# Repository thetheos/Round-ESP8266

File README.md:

# Round-ESP8266
carte micro-controller ESP8266 intégre à un pcb rond avec pile lithium et rechage via QI

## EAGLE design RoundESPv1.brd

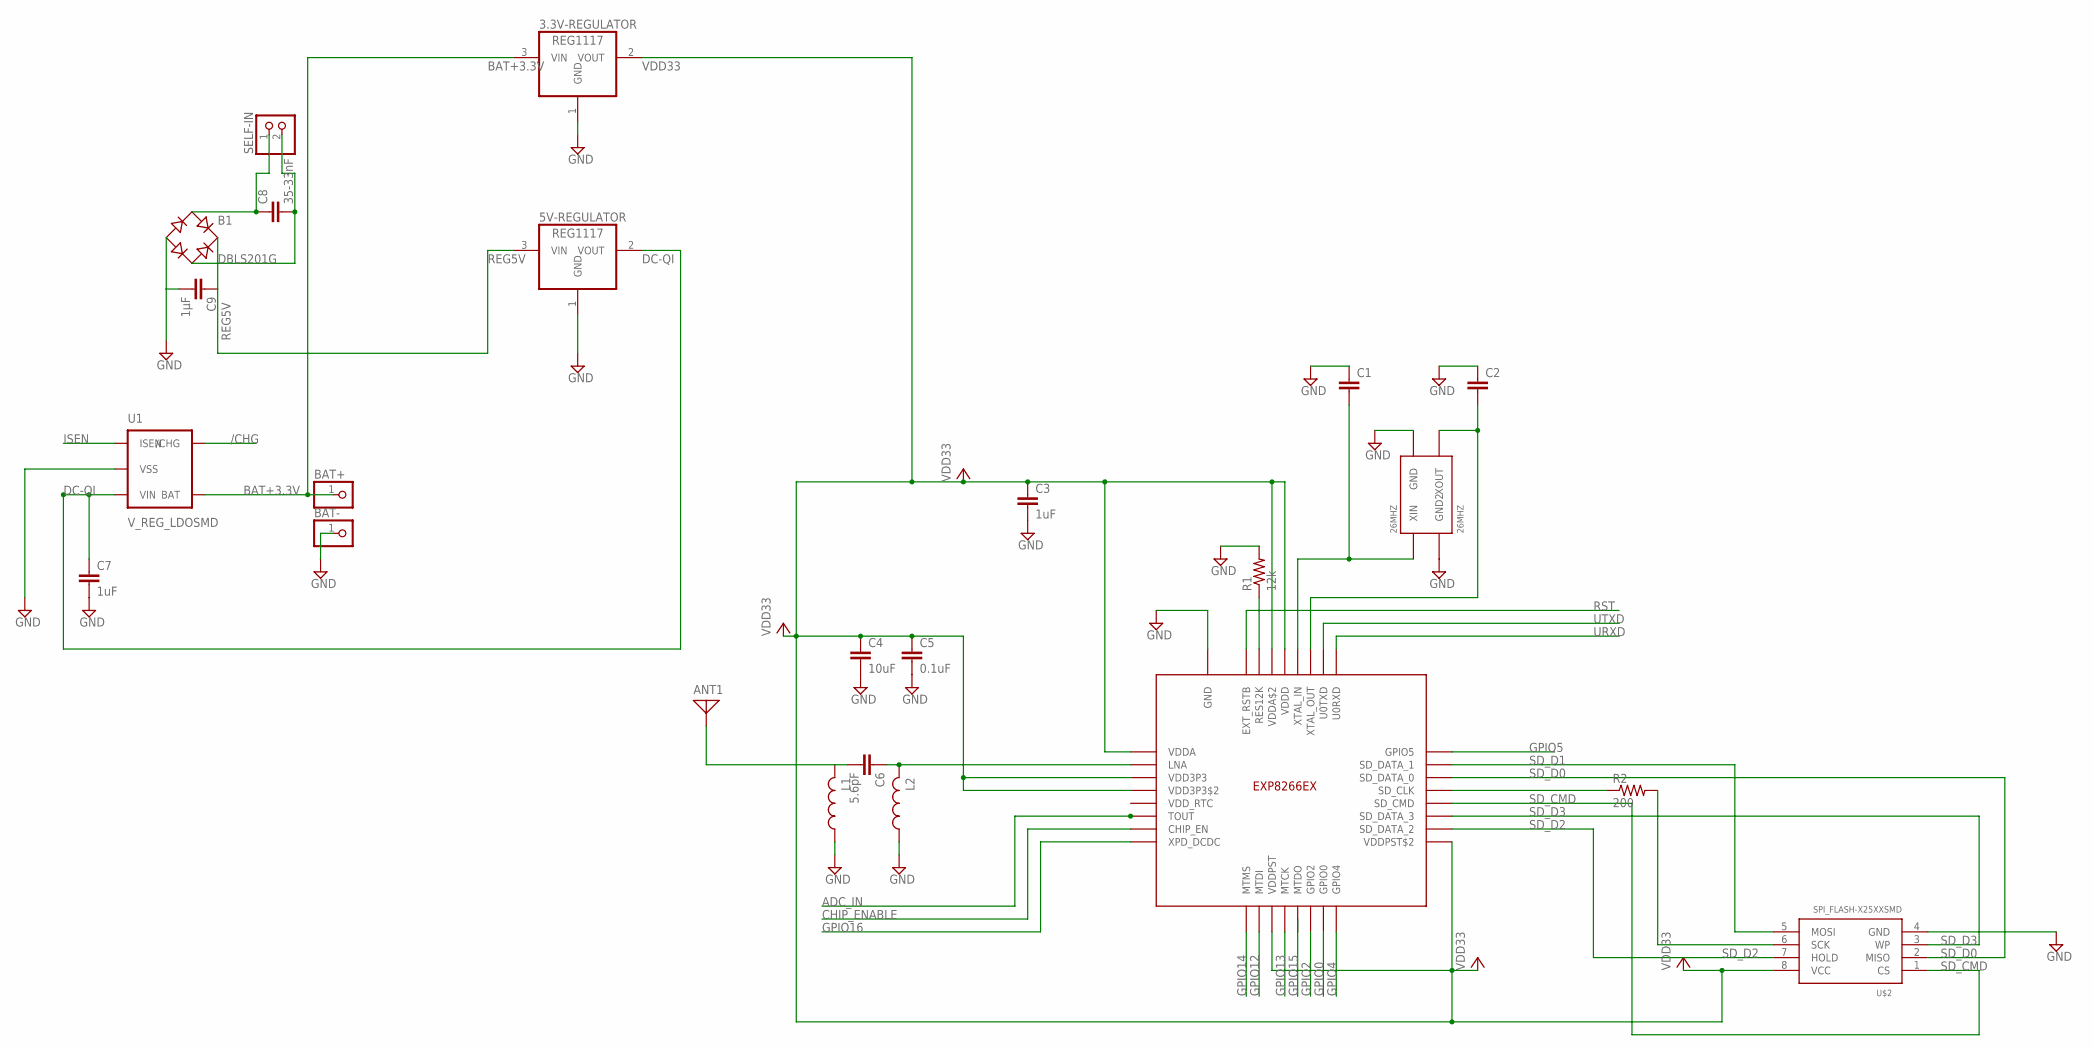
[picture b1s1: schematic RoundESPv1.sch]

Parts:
3.3V-REGULATOR, 5V-REGULATOR: REG1117; SOT223
26MHZ: 26MHZ; CRYSTAL-OSC-SMD-5X3.2
ANT1: ANTENNA; PAD-01
B1: DBLS201G; DBS
BAT+: PINHD-1X1; 1X01
BAT-: PINHD-1X1; 1X01
C1, C2: C2,5-3; C2.5-3
C3, C7: 1uF; C2.5-3
C4: 10uF; C2.5-3
C5: 0.1uF; C2.5-3
C6: 5.6pF; C2.5-3
C8: 35-33nF; C2.5-3
C9: 1µF; C2.5-3
L1, L2: L-USL2012C; L2012C
R1: 12k; M0805
R2: 200; M0805
SELF-IN: PINHD-1X2; 1X02
U1: V_REG_LDOSMD; SOT23-5
U2: ESP8266EX
U$2: SPI_FLASH-X25XXSMD; SO08

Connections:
/CHG: U1.5 (/CHG)
ADC_IN: U2.TOUT
BAT+3.3V: 3.3V-REGULATOR.3 (VIN), BAT+.1, U1.4 (BAT)
CHIP_ENABLE: U2.CHIP_EN
DC-QI: 5V-REGULATOR.2 (VOUT), C7.1, U1.2 (VIN)
GND: 3.3V-REGULATOR.1 (GND), 5V-REGULATOR.1 (GND), 26MHZ.1 (GND2), 26MHZ.3 (GND), B1.-, BAT-.1, C1.1, C2.1, C3.2, C4.2, C5.2, C7.2, C9.2, L1.1, L2.1, R1.2, U1.3 (VSS), U2.GND, U$2.4 (GND)
GPIO0: U2.GPIO0
GPIO2: U2.GPIO2
GPIO4: U2.GPIO4
GPIO5: U2.GPOIO5 (GPIO5)
GPIO12: U2.MTDI
GPIO13: U2.MTCK
GPIO14: U2.MTMS
GPIO15: U2.MTDO
GPIO16: U2.XPD_DCDC
ISEN: U1.1 (ISEN)
unnamed: 26MHZ.2 (XOUT), C2.2, U2.XTAL_OUT
unnamed: C6.1, L2.2, U2.LNA
unnamed: ANT1.1, C6.2, L1.2
unnamed: 26MHZ.4 (XIN), C1.2, U2.XTAL_IN
unnamed: R1.1, U2.RES12K
unnamed: B1.AC1, C8.1, SELF-IN.1
unnamed: B1.AC2, C8.2, SELF-IN.2
unnamed: R2.1, U2.SD_CLK
unnamed: R2.2, U$2.6 (SCK)
REG5V: 5V-REGULATOR.3 (VIN), B1.+, C9.1
RST: U2.EXT_RSTB
SD_CMD: U2.SD_CMD, U$2.1 (CS)
SD_D0: U2.SD_DATA_0, U$2.2 (MISO)
SD_D1: U2.SD_DATA_1, U$2.5 (MOSI)
SD_D2: U2.SD_DATA_2, U$2.7 (HOLD)
SD_D3: U2.SD_DATA_3, U$2.3 (WP)
URXD: U2.U0RXD
UTXD: U2.U0TXD
VDD33: 3.3V-REGULATOR.2 (VOUT), C3.1, C4.1, C5.1, U2.VDD3P3, U2.VDD3P3$2, U2.VDDA, U2.VDDA$2, U2.VDDD, U2.VDDPST, U2.VDDPST$2, U$2.8 (VCC)

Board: 4 copper layers, 24 parts (0 on the bottom side), 19 nets, no tracks yet.

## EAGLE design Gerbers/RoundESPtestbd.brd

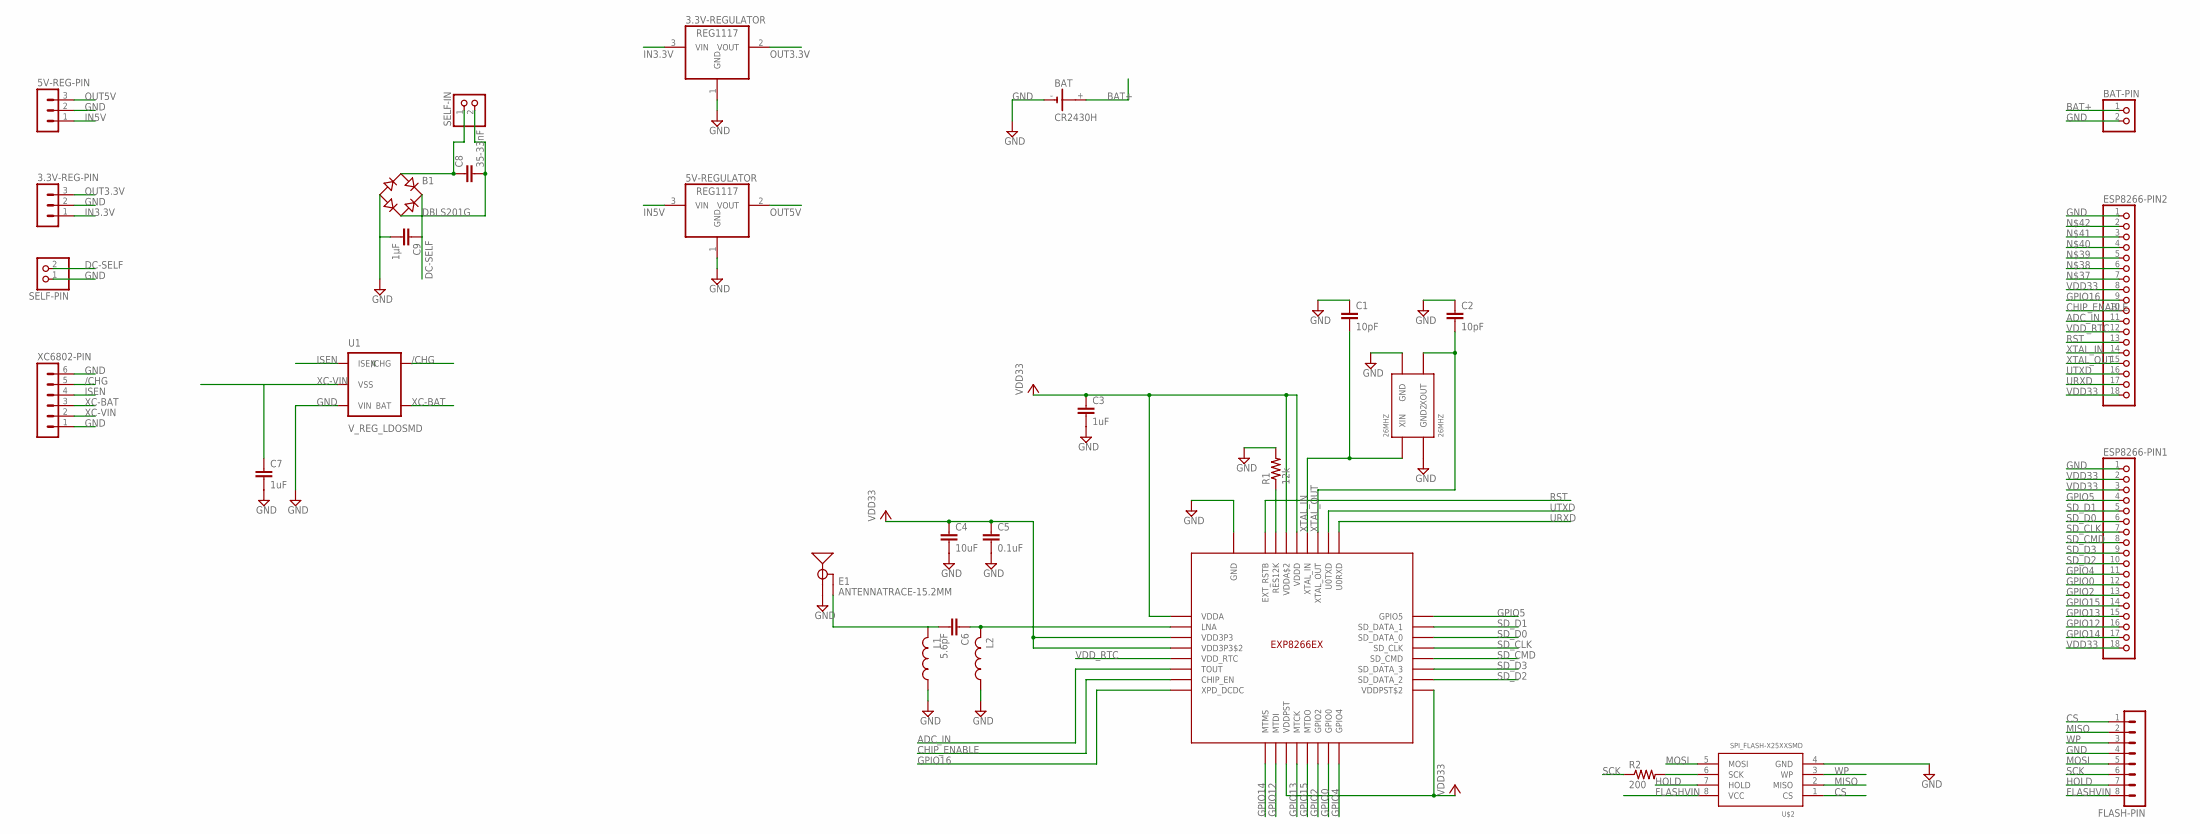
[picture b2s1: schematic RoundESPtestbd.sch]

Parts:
3.3V-REG-PIN, 5V-REG-PIN: MA03-1
3.3V-REGULATOR, 5V-REGULATOR: REG1117; SOT223
26MHZ: 26MHZ; CRYSTAL-OSC-SMD-5X3.2
B1: DBLS201G; DBS
BAT: CR2430H
BAT-PIN: PINHD-1X2; 1X02
C1, C2: 10pF; C2.5-3
C3, C7: 1uF; C2.5-3
C4: 10uF; C2.5-3
C5: 0.1uF; C2.5-3
C6: 5.6pF; C2.5-3
C8: 35-33nF; C2.5-3
C9: 1µF; C2.5-3
E1: ANTENNATRACE-15.2MM; TRACE_ANTENNA_2.4GHZ_15.2MM
ESP8266-PIN1, ESP8266-PIN2: PINHD-1X18; 1X18
FLASH-PIN: MA08-1
L1, L2: L-USL2012C; L2012C
R1: 12k; M0805
R2: 200; M0805
SELF-IN: PINHD-1X2; 1X02
SELF-PIN: PINHD-1X2; 1X02
U1: V_REG_LDOSMD; SOT23-5
U2: ESP8266EX
U$2: SPI_FLASH-X25XXSMD; SO08
XC6802-PIN: MA06-1

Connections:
111: R2.2, U$2.6 (SCK)
/CHG: U1.5 (/CHG), XC6802-PIN.5
ADC_IN: ESP8266-PIN2.11, U2.TOUT
BAT+: BAT.+, BAT-PIN.1
CHIP_ENABLE: ESP8266-PIN2.10, U2.CHIP_EN
CS: FLASH-PIN.1, U$2.1 (CS)
DC-SELF: B1.+, C9.1, SELF-PIN.2
FLASHVIN: FLASH-PIN.8, U$2.8 (VCC)
GND: 3.3V-REG-PIN.2, 3.3V-REGULATOR.1 (GND), 5V-REG-PIN.2, 5V-REGULATOR.1 (GND), 26MHZ.1 (GND2), 26MHZ.3 (GND), B1.-, BAT.-, BAT-PIN.2, C1.1, C2.1, C3.2, C4.2, C5.2, C9.2, E1.ANT (SIGNAL), ESP8266-PIN1.1, ESP8266-PIN2.1, FLASH-PIN.4, L1.1, L2.1, R1.2, SELF-PIN.1, U1.2 (VIN), U2.GND, U$2.4 (GND), XC6802-PIN.1, XC6802-PIN.6
GPIO0: ESP8266-PIN1.12, U2.GPIO0
GPIO2: ESP8266-PIN1.13, U2.GPIO2
GPIO4: ESP8266-PIN1.11, U2.GPIO4
GPIO5: ESP8266-PIN1.4, U2.GPOIO5 (GPIO5)
GPIO12: ESP8266-PIN1.16, U2.MTDI
GPIO13: ESP8266-PIN1.15, U2.MTCK
GPIO14: ESP8266-PIN1.17, U2.MTMS
GPIO15: ESP8266-PIN1.14, U2.MTDO
GPIO16: ESP8266-PIN2.9, U2.XPD_DCDC
HOLD: FLASH-PIN.7, U$2.7 (HOLD)
IN3.3V: 3.3V-REG-PIN.1, 3.3V-REGULATOR.3 (VIN)
IN5V: 5V-REG-PIN.1, 5V-REGULATOR.3 (VIN)
ISEN: U1.1 (ISEN), XC6802-PIN.4
MISO: FLASH-PIN.2, U$2.2 (MISO)
MOSI: FLASH-PIN.5, U$2.5 (MOSI)
unnamed: C6.1, L2.2, U2.LNA
unnamed: C6.2, E1.GND, L1.2
unnamed: R1.1, U2.RES12K
unnamed: B1.AC1, C8.1, SELF-IN.1
unnamed: B1.AC2, C8.2, SELF-IN.2
OUT3.3V: 3.3V-REG-PIN.3, 3.3V-REGULATOR.2 (VOUT)
OUT5V: 5V-REG-PIN.3, 5V-REGULATOR.2 (VOUT)
RST: ESP8266-PIN2.13, U2.EXT_RSTB
SCK: FLASH-PIN.6, R2.1
SD_CLK: ESP8266-PIN1.7, U2.SD_CLK
SD_CMD: ESP8266-PIN1.8, U2.SD_CMD
SD_D0: ESP8266-PIN1.6, U2.SD_DATA_0
SD_D1: ESP8266-PIN1.5, U2.SD_DATA_1
SD_D2: ESP8266-PIN1.10, U2.SD_DATA_2
SD_D3: ESP8266-PIN1.9, U2.SD_DATA_3
URXD: ESP8266-PIN2.17, U2.U0RXD
UTXD: ESP8266-PIN2.16, U2.U0TXD
VDD33: C3.1, C4.1, C5.1, ESP8266-PIN1.2, ESP8266-PIN1.3, ESP8266-PIN1.18, ESP8266-PIN2.8, ESP8266-PIN2.18, U2.VDD3P3, U2.VDD3P3$2, U2.VDDA, U2.VDDA$2, U2.VDDD, U2.VDDPST, U2.VDDPST$2
VDD_RTC: ESP8266-PIN2.12, U2.VDD_RTC
WP: FLASH-PIN.3, U$2.3 (WP)
XC-BAT: U1.4 (BAT), XC6802-PIN.3
XC-VIN: C7.1, U1.3 (VSS), XC6802-PIN.2
XTAL_IN: 26MHZ.4 (XIN), C1.2, ESP8266-PIN2.14, U2.XTAL_IN
XTAL_OUT: 26MHZ.2 (XOUT), C2.2, ESP8266-PIN2.15, U2.XTAL_OUT

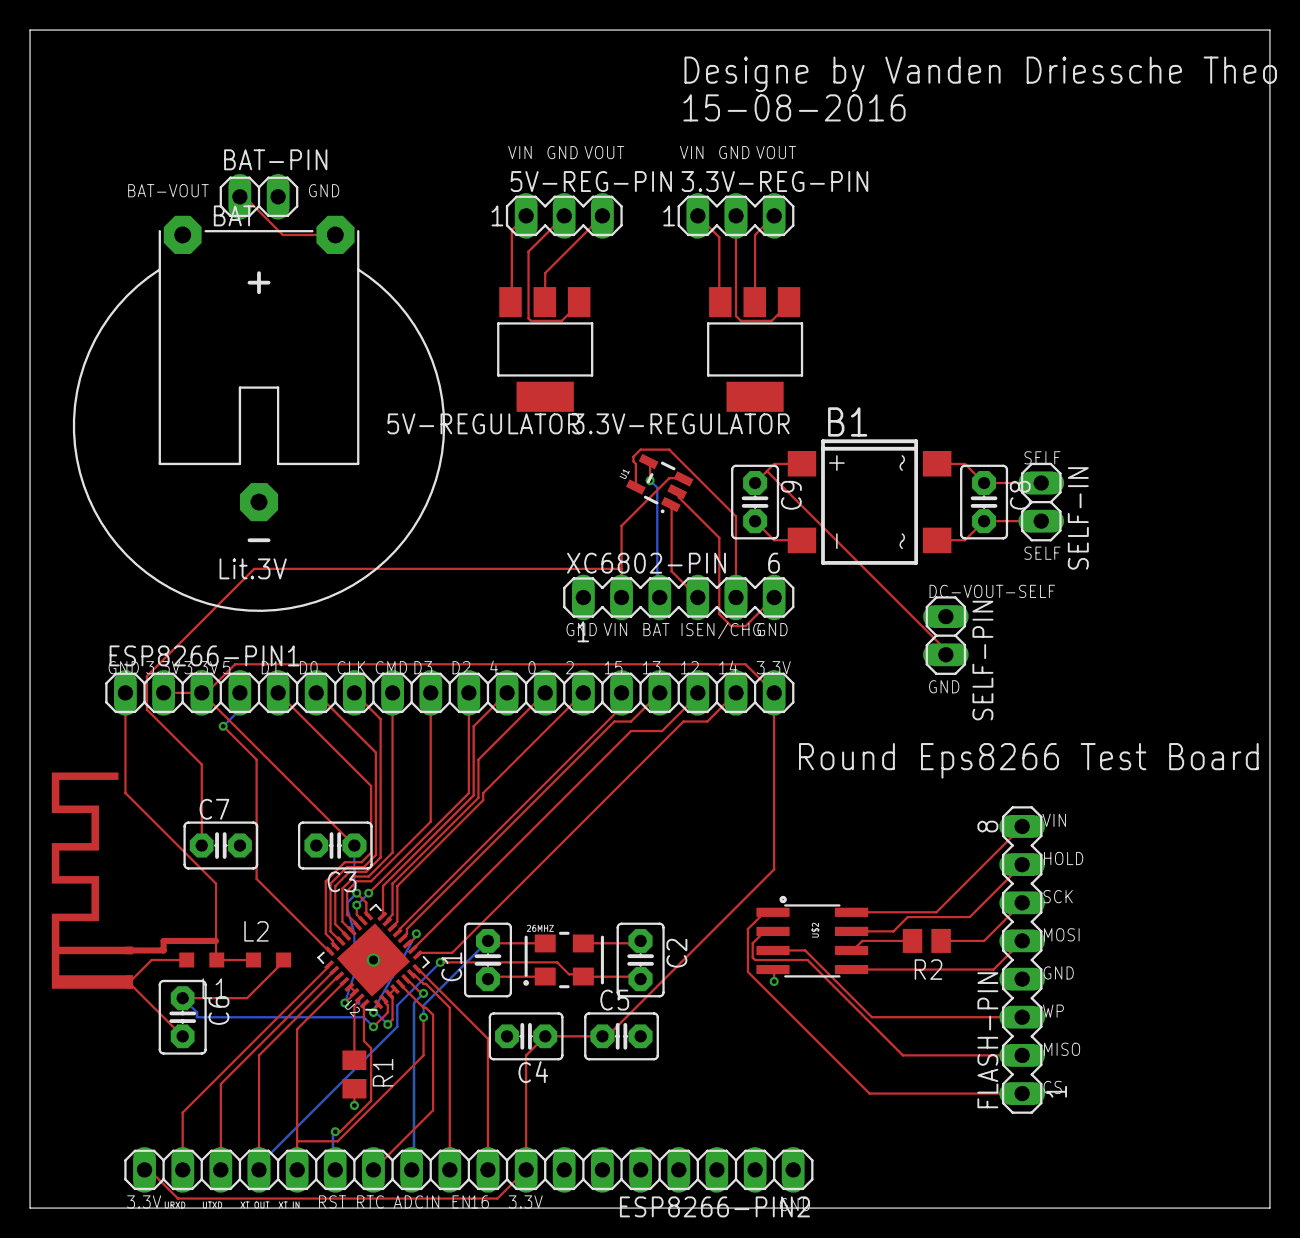
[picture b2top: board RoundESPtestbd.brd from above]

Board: 2 copper layers, 82.5 x 78.4 mm, 31 parts (0 on the bottom side), 48 nets.

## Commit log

2016-08-22 Create Gerber

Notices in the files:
parts and their libraries:
SparkFun-FreqCtrl: Licensing: Creative Commons ShareAlike 4.0 International - https://creativecommons.org/licenses/by-sa/4.0
